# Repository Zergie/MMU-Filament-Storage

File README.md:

<p align="center">

</p>

YAMMU is an open, Voron-inspired multi-material unit for FFF printers. It combines eight filament paths, enclosed heated storage, BLDC-driven loading, filament sensing, custom electronics, and Klipper-based control in one machine.

> [!IMPORTANT]
> **YAMMU is a work in progress.** The current goal is reliable loading and unloading before or at the start of a print. Multi-color and multi-material printing are planned, but are not the present focus.

## See the machine

| Complete enclosure | Twin spool carrier | Heated chamber | Custom electronics bay |
| :---: | :---: | :---: | :---: |
|  |  |  |  |

## One system, four jobs

- **Store** — eight spools live in two enclosed drawers built around 2020 extrusion.
- **Dry** — the sealed filament chamber is heated for dry storage while printing.
- **Move** — two BLDC-driven feeders load filament through short inlet paths and toward the extruder.
- **Verify** — switches at the splitter and toolhead let the control system confirm filament progress.

## Built as open hardware

The repository contains the mechanical, electrical, firmware, and assembly material needed to follow the project—not just product renders.

| Area | What is included | Start here |
| --- | --- | --- |
| Mechanical | STEP assembly, printable STLs, and panel DXFs | [CAD](./CAD) · [STLs](./STLs) · [DXFs](./Drawings_DXFs) |
| Electronics | Main, connector, and sensor-board source and manufacturing files | [PCB files](./PCB) - new version soon! |
| Firmware | RP2040 build notes and YAMMU configuration for Klipper / Happy Hare | [Firmware guide](./Firmware/README.md) - new version soon! |
| Assembly | Illustrated assembly manual | [Open the PDF](./Manual/Assembly.pdf) |

## Start exploring

1. Inspect the [STEP assembly](./CAD/Assembly.step) or browse the ready-to-print [STLs](./STLs).
2. Read the [assembly manual](./Manual/Assembly.pdf) to understand the current mechanical build.
3. (unfinished) Review the [PCB feature set](./PCB/README.md) and manufacturing files.
4. (unfinished) Follow the [firmware guide](./Firmware/README.md) for the current RP2040, Klipper, and Happy Hare setup.

## Current roadmap

[View v1.0 progress](https://github.com/Zergie/YAMMU/issues?q=is%3Aissue%20milestone%3Av1.0)
[View v1.1 progress](https://github.com/Zergie/YAMMU/issues?q=is%3Aissue%20milestone%3Av1.1)

## Help build YAMMU

The project especially needs help with prototype testing, CAD, electronics, firmware, and documentation. If you can test the current iteration or improve one part of the system, open an issue or pull request—or join the [YAMMU Discord](https://discord.gg/QSjW5CMHZC).

## Credits and related projects

YAMMU builds on ideas and parts from the wider open-source 3D-printing community, including [Voron Trident](https://github.com/VoronDesign/Voron-Trident), [ERCF v2](https://github.com/Enraged-Rabbit-Community/ERCF_v2), and several community designs documented in the repository history. Review source licenses before redistributing derived parts.

<details>
<summary><strong>Third-party parts and original licenses</strong></summary>

- [Voron Trident](https://github.com/VoronDesign/Voron-Trident) parts — GNU GPL v3
- [ERCF v2](https://github.com/Enraged-Rabbit-Community/ERCF_v2) parts — GNU GPL v3
- [Stronger Compact Spool Auto-Rewinder](https://www.printables.com/model/784434-stronger-compact-spool-auto-rewinder) by rans_1668459 — GNU GPL v2
- [Voron 2.4 front panel handle, hinge, and magnet latch](https://www.printables.com/model/371692-voron-24-front-panel-handle-hinge-magnet-latch/files) by Jason_116929 — CC BY-SA
- [Removable panel/door kit for Voron V2/Trident](https://www.printables.com/model/702768-kit-for-removable-panelsdoors-for-voron-v2trident-/files) by Victor Mateus Oliveira — GNU GPL v3
- [WAGO 221-415 extrusion mount](https://www.printables.com/model/869020-wago-221-415-extrusion-mount-1by5-and-2by5) by Artxime — GNU GPL v3
- [LRS-200 DIN rail mount](https://www.printables.com/model/254538-lrs-200-din-rail-mount) by CrazyIvan359 — Creative Commons 4.0

</details>

Other MMU projects worth exploring include [ERCF v2](https://github.com/Enraged-Rabbit-Community/ERCF_v2), [8-Track](https://github.com/ArmoredTurtle/8-Track-Raven-Alpha), [Primitive Infinite Spool System](https://github.com/Esoterical/PrinterMods/tree/main/Primitive%20Infinite%20Spool%20System), [TradRack](https://github.com/Annex-Engineering/TradRack), and Prusa MMU3.

## License

Repository content is provided under the [GNU General Public License v3.0](./LICENSE). Third-party parts retain their original licenses.

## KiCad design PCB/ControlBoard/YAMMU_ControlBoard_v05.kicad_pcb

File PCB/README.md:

<p align="center">

</p>

This directory contains the editable KiCad design and manufacturing data for the **YAMMU Control Board v05**. The 100 × 60 mm board brings the RP2040 controller, motor and heater control, fan outputs, servos, end stops, analog sensors, I²C, and power regulation onto one board.

## Board preview

| Component side | Solder side |
| :---: | :---: |
|  |  |

| Design fact | Checked-in value |
| --- | --- |
| Board revision | `05` |
| KiCad format | KiCad `9.0` |
| Outline | approximately `100 × 60 mm` |
| Board thickness | `1.6 mm` |
| Copper stack | `4 layers` |
| Assembly side | Top-side placement data; the bottom placement file contains no components |
| Placement records | 220 top-side entries |
| DRC snapshot | [0 violations, 0 unconnected pads](./ControlBoard/DRC.rpt) on 2026-07-11 |

## Find the right file

| Use | File |
| --- | --- |
| Open the complete design | [`YAMMU_ControlBoard_v05.kicad_pro`](./ControlBoard/YAMMU_ControlBoard_v05.kicad_pro) |
| Edit the PCB | [`YAMMU_ControlBoard_v05.kicad_pcb`](./ControlBoard/YAMMU_ControlBoard_v05.kicad_pcb) |
| Read the schematic | [Schematic PDF](./ControlBoard/OutputJob/Schematics/YAMMU_ControlBoard_v05.pdf) |
| Manufacture bare boards | [Gerber + drill ZIP](./ControlBoard/OutputJob/YAMMU_ControlBoard_v05_Gerber.zip) |
| Order SMT assembly | [BOM](./ControlBoard/OutputJob/BOM/YAMMU_ControlBoard_v05_BOM.xlsx) + [top-side CPL](./ControlBoard/OutputJob/Centroid/TopCentroid.xlsx) |
| Hand-assemble or inspect | [Interactive BOM](./ControlBoard/Interactive%20Bom/ibom.html) |
| Check component outlines | [Front fabrication drawing](./ControlBoard/OutputJob/BestPlan/YAMMU_ControlBoard_v05-F_Fab.pdf) · [Back fabrication drawing](./ControlBoard/OutputJob/BestPlan/YAMMU_ControlBoard_v05-B_Fab.pdf) |

## Order a bare PCB

[JLCPCB](https://jlcpcb.com/) is one example board house; the same release files can be used with another manufacturer. Prices, capabilities, and form labels change, so treat the provider's current documentation as authoritative.

1. Open the board house's PCB quote page and upload the **ZIP itself**. For JLCPCB, use the [Gerber + drill ZIP](./ControlBoard/OutputJob/YAMMU_ControlBoard_v05_Gerber.zip).
2. Compare the detected result with the design: approximately **100 × 60 mm**, **4 copper layers**, and **1.6 mm** finished thickness. Select the required material, copper weight, solder-mask color, surface finish, quantity, and any other fabrication options; do not rely on automatic detection for choices that are not encoded in the Gerbers.
3. Open the provider's Gerber viewer. Inspect all four copper layers, the continuous board outline, all drills and slots, both masks, and both silkscreens.
4. Save the item to the cart, review manufacturing warnings, shipping, tax, and lead time, then submit the order.

JLCPCB's current walkthrough is available in its [official PCB ordering guide](https://jlcpcb.com/help/article/how-do-i-place-an-order). The online preview is a useful final check, but it does not replace reviewing the KiCad design and release contents.

## Order SMT assembly

An assembly order needs three data sets:

| Upload | What it tells the assembler | This repository |
| --- | --- | --- |
| **Gerbers + drills** | How to fabricate the bare board | [`YAMMU_ControlBoard_v05_Gerber.zip`](./ControlBoard/OutputJob/YAMMU_ControlBoard_v05_Gerber.zip) |
| **BOM** | Which part belongs at each reference designator | [`YAMMU_ControlBoard_v05_BOM.xlsx`](./ControlBoard/OutputJob/BOM/YAMMU_ControlBoard_v05_BOM.xlsx) |
| **CPL / centroid / pick-and-place** | Each component's X/Y position, rotation, and board side | [`TopCentroid.xlsx`](./ControlBoard/OutputJob/Centroid/TopCentroid.xlsx) |

The BOM contains `Designator`, `Comment`, `Footprint`, `Amount`, and `JLCPCB Part #` columns. The CPL contains `Designator`, `Mid X`, `Mid Y`, `Rotation`, and `Layer`. The reference designators must match between the two files.

For a JLCPCB PCBA order:

1. Start a PCB order, upload the corrected Gerber ZIP, and enable **PCB Assembly** before checkout.
2. Select top-side assembly. The current top CPL has 220 placement records. The bottom CPL has no components and is not used for assembly.
3. Upload the BOM and top-side CPL, then let the service process and match them.
4. Review every unmatched or substituted component. Confirm value, package, manufacturer part number or JLCPCB/LCSC part number, stock, and quantity. “No part selected” means that item will not be fitted.
5. Inspect the placement preview at high zoom. Check connector orientation, polarized capacitors and diodes, IC pin 1, rotations, and the board origin. Do not approve the job solely because the files were accepted.
6. Confirm which through-hole, module, connector, or otherwise unsupported parts must be installed by hand after delivery.

JLCPCB documents the current flow in its [official PCBA ordering guide](https://jlcpcb.com/help/article/how-do-i-place-a-pcba-order). Its [BOM/CPL preparation guidance](https://jlcpcb.com/help/article/advice-for-bom-and-cpl-files-preparation) explains reference matching, supported headers, coordinates, and common upload problems.

> [!IMPORTANT]
> Component availability and assembly capabilities are live manufacturing constraints, not properties of this repository. Always re-check part matches and the placement preview for the specific order.

## Use the Interactive BOM

[`Interactive Bom/ibom.html`](./ControlBoard/Interactive%20Bom/ibom.html) is a self-contained browser view generated from the PCB. Download or clone the repository and open the file locally—no KiCad installation or web server is required.

Use it to:

- click a BOM row and highlight the matching footprints on the board;
- pan, zoom, and switch between board sides;
- search by reference, value, or footprint;
- group identical parts and inspect their board locations;
- tick off parts while hand-placing or checking a finished assembly.

The Interactive BOM is an **assembly and inspection aid**. It is not the BOM spreadsheet, not pick-and-place data, and not a file to upload for SMT assembly. Use the `.xlsx` BOM and CPL listed above for the manufacturer.

## License

This PCB is part of the YAMMU open-hardware project. See the repository's [GNU GPL v3.0 license](../LICENSE).

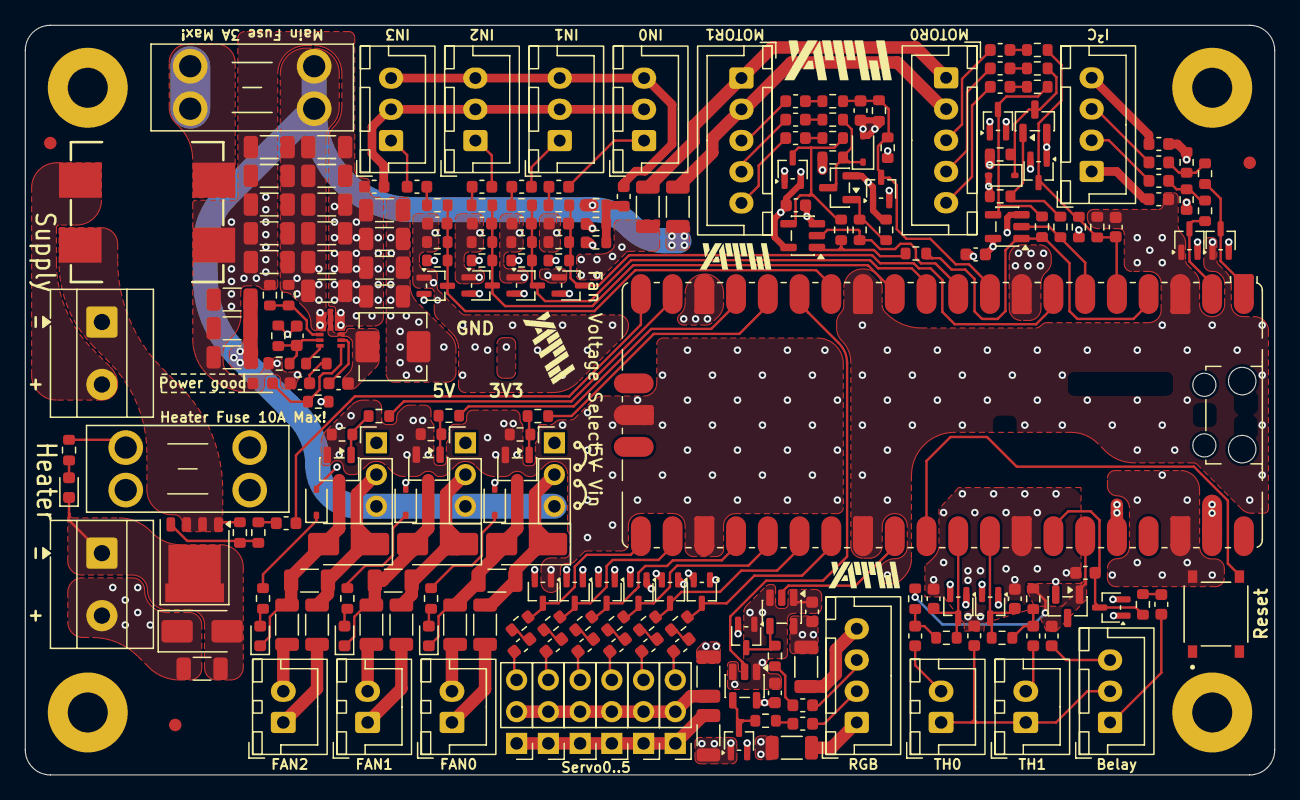
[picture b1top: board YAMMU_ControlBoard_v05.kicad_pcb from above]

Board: 8 copper layers, 100.0 x 60.0 mm, 234 parts (0 on the bottom side), 137 nets.

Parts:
C1, C3: 1nF; C_0603_1608Metric
C1.1, C1.2, C1.3, C1.4, C1.5, C1.6, C1.7, C7, C8, C9, C10, C11, C12, C13: 10µF 50V; C_1206_3216Metric
C2, C4, C5, C14: 10nF; C_0603_1608Metric
C2.1, C2.2, C2.3, C2.4: 100µF/6,3V; C_1206_3216Metric
C3.1, C16, C17, C20, C21, C22, C23, C24: 100nF; C_0603_1608Metric
C4.1: 47pF; C_0603_1608Metric
C5.1: 3,3nF; C_0603_1608Metric
C6, C15, C18, C19: 2,2µF; C_1206_3216Metric
D1, D2, D3, D4, D6, D7, D8, D9, D11, D15, D17, D21, D22, D23, D24, D25, D31, D32, D33, D34, D35: BAT54SW; SOT-323_SC-70
D5, D10: BZT52C4V7S; D_SOD-323
D12, D16, D18, D27, D28: RED; LED_0603_1608Metric
D13, D19, D29: 1N4148; D_SOD-323
D14, D20, D26, D30: SS34; D_SMA
F1: 3A; Fuseholder_Blade_Mini_Keystone_3568
F2: 10A; Fuseholder_Blade_Mini_Keystone_3568
FB1, FB2, FB3, FB4, FB5, FB6, FB7, FB8, FB9, FB10, FB11, FB13, FB15, FB16, FB18, FB20, FB21, FB22, FB23, FB24, FB25, FB26, FB34, FB36, FB38, FB39, FB40, FB41, FB42, FB43: 600Ohm 200mA; L_0603_1608Metric
FB12, FB14, FB17, FB19, FB28, FB29, FB30, FB31, FB32, FB33, FB35, FB37: 600Ohm 3A; L_1206_3216Metric
FID1, FID2, FID3: Fiducial; Fiducial_1mm_Mask2mm
H1, H2, H3, H4: M3; MountingHole_3.2mm_M3_Pad
IC1: AP63356DV-7; AP63356DV7
IC2: RaspberryPi_Pico; RaspberryPi_Pico_SMD_HandSolder
J1, J4, J7, J11, J23: Conn_01x03; JST_XH_B3B-XH-A_1x03_P2.50mm_Vertical
J2, J5: Conn_01x05; JST_XH_B5B-XH-A_1x05_P2.50mm_Vertical
J3, J6, J10, J13, J15, J17: Conn_01x03_Pin; PinHeader_1x03_P2.54mm_Vertical_HighDensity
J8, J12, J14, J16, J20: Conn_01x02; JST_XH_B2B-XH-A_1x02_P2.50mm_Vertical
J9, J19: Screw_Terminal_01x02; JL301-50002U02
J21, J22: Conn_01x04; JST_XH_B4B-XH-A_1x04_P2.50mm_Vertical
JP2, JP3, JP4: Jumper_3_Open; PinHeader_1x03_P2.54mm_Vertical_HighDensity
L1: 6,8µH; L_APV_APH0530
L2: 1kΩ@100MHz 2 6A 80V; ACM1211
Q1, Q2: 2N7002; SOT-23
Q3, Q4, Q6: AO3400A; SOT-23-3
Q5: HY1904C2; PQFN-8-EP_6x5mm_P1.27mm_Generic
R1, R14, R35, R36, R37, R64: 0R; R_0603_1608Metric
R1.1: 105K; R_0603_1608Metric
R2, R3, R6, R7, R10, R15, R16, R19, R20, R23, R28, R30, R39, R41: 150K; R_0603_1608Metric
R2.1, R51: 20K; R_0603_1608Metric
R3.1, R13, R26, R34, R44, R45, R48, R53, R56: 47K; R_0603_1608Metric
R4, R4.1, R5, R17, R18, R29, R40: 10K; R_0603_1608Metric
R5.1: 38K3; R_0603_1608Metric
R8, R9, R11, R21, R22, R24, R32, R42, R47, R50, R57, R58: 220R; R_0603_1608Metric
R12, R25, R33, R43, R52, R55, R60, R62: 100R; R_0603_1608Metric
R27, R31, R38, R54: 1K; R_0603_1608Metric
R46, R49, R59, R61, R63: 4K7; R_0603_1608Metric
SW1: SW_MEC_5E; SW_TS-1187A-B-A-B
U1, U2: SN74AHCT1G86DBVR; SOT-23-5
U3: LM4040A30IDBZR; SOT-23
U4, U5: SN74AHCT1G125DBVR; SOT-23-5

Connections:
+3V3: C23.1, C24.1, D1.2 (K), D2.2 (K), D3.2 (K), D4.2 (K), D6.2 (K), D7.2 (K), D8.2 (K), D9.2 (K), D11.2 (K), D13.2 (A), D15.2 (K), D17.2 (K), D19.2 (A), D21.2 (K), D22.2 (K), D23.2 (K), D24.2 (K), D25.2 (K), D29.2 (A), D33.2 (K), D34.2 (K), D35.2 (K), FB39.2, IC2.36 (3V3), R2.1, R3.1, R15.1, R16.1, R28.1, R31.1, R35.1, R39.1, R59.2, R61.2, U1.5 (VCC), U2.5 (VCC)
+5V: C2.1.1, C2.2.1, C2.3.1, C2.4.1, C4.1.2, C20.1, C21.1, D31.2 (K), D32.2 (K), FB30.2, FB35.1, IC2.39 (VSYS), JP2.1 (A), JP3.1 (A), JP4.1 (A), L1.2, R1.1.1, R36.1, U4.5 (VCC), U5.5 (VCC)
/AnalogSensors/AnalogSignals.Belay: C22.1, D35.3 (COM), IC2.34 (GPIO28_ADC2), R63.2
/AnalogSensors/AnalogSignals.TH0: C16.1, D22.3 (COM), IC2.31 (GPIO26_ADC0), R46.2
/AnalogSensors/AnalogSignals.TH1: C17.1, D24.3 (COM), IC2.32 (GPIO27_ADC1), R49.2
/AnalogSensors/Belay/GNDsensor: FB23.2, J14.1, J16.1, J23.2
/AnalogSensors/Vref: FB42.2, IC2.35 (ADC_VREF), R45.1, R48.1, U3.1 (K)
/EndStops/EndStop0: C2.1, D2.3 (COM), IC2.7 (GPIO5), R3.2, R5.2, R7.1
/EndStops/EndStop1: C4.1, D7.3 (COM), IC2.11 (GPIO8), R16.2, R18.2, R20.1
/EndStops/EndStop2: C5.1, D11.3 (COM), IC2.12 (GPIO9), R28.2, R29.2, R30.1
/EndStops/EndStop3: C14.1, D17.3 (COM), IC2.14 (GPIO10), R39.2, R40.2, R41.1
/EndStops/Input0/GNDin: FB20.2, J1.2, J4.2, J7.2, J11.2
/EndStops/Input0/Input_In: FB1.1, J1.1
/EndStops/Input0/Vin: FB15.1, J1.3, J4.3, J7.3, J11.3
/EndStops/Input1/Input_In: FB6.1, J4.1
/EndStops/Input2/Input_In: FB11.1, J7.1
/EndStops/Input3/Input_In: FB16.1, J11.1
/FansOut/FanEnable0: IC2.16 (GPIO12), R33.1
/FansOut/FanEnable1: IC2.17 (GPIO13), R43.1
/FansOut/FanEnable2: IC2.19 (GPIO14), R55.1
/FansOut/FanOut0/1N4148_A: D13.1 (K), R27.1
/FansOut/FanOut0/Fout+: FB12.2, J8.1
/FansOut/FanOut0/Fout-: FB14.1, J8.2
/FansOut/FanOut0/Gate: Q3.1 (G), R33.2, R34.1
/FansOut/FanOut0/LED_A: D12.2 (A), R27.2
/FansOut/FanOut1/1N4148_A: D19.1 (K), R38.1
/FansOut/FanOut1/Fout+: FB17.2, J12.1
/FansOut/FanOut1/Fout-: FB19.1, J12.2
/FansOut/FanOut1/Gate: Q4.1 (G), R43.2, R44.1
/FansOut/FanOut1/LED_A: D18.2 (A), R38.2
/FansOut/FanOut2/1N4148_A: D29.1 (K), R54.1
/FansOut/FanOut2/Fout+: FB31.2, J20.1
/FansOut/FanOut2/Fout-: FB32.1, J20.2
/FansOut/FanOut2/Gate: Q6.1 (G), R55.2, R56.1
/FansOut/FanOut2/LED_A: D28.2 (A), R54.2
/HeaterOut/EN_IN: FB26.1, R52.1
/HeaterOut/Enable: FB26.2, IC2.20 (GPIO15)
/HeaterOut/Gate: Q5.4 (G), R52.2, R53.1
/HeaterOut/Hout+: C18.1, D26.1 (K), F2.2, J19.2, R51.1
/HeaterOut/Hout-: C18.2, D26.2 (A), D27.1 (K), J19.1, Q5.5 (D)
/HeaterOut/LED_A: D27.2 (A), R51.2
/HeaterOut/Vin+: F2.1, J9.2, L2.1
/I²C_Out/SCL_Out: FB40.2, J22.2
/I²C_Out/SDA_Out: FB38.2, J22.3
/MCU/BLDC0.DIR: IC2.4 (GPIO2), R14.1, R64.1, U2.1
/MCU/BLDC0.PWM: IC2.6 (GPIO4), R25.1, U2.2
/MCU/BLDC0.TACHO: C3.1, D6.3 (COM), IC2.5 (GPIO3), R15.2, R17.1, R19.1
/MCU/BLDC1.PWM: IC2.10 (GPIO7), R12.1, U1.2
/MCU/BLDC1.TACHO: C1.1, D1.3 (COM), IC2.9 (GPIO6), R2.2, R4.1, R6.1
/MCU/I2C.SCL: D34.3 (COM), IC2.2 (GPIO1), R62.1
/MCU/I2C.SDA: D33.3 (COM), IC2.1 (GPIO0), R60.1
/MCU/RGB.CLK: IC2.15 (GPIO11), U5.2
/MCU/RGB.DATA: IC2.29 (GPIO22), U4.2
/Motors/BLDC0/DIR_Mot: FB8.1, J5.5
/Motors/BLDC0/GND_Mot: FB29.1, J2.1, J5.1
/Motors/BLDC0/PWM_Mot: FB10.1, J5.4
/Motors/BLDC0/Tacho_Mot: FB7.2, J5.3
/Motors/BLDC0/V_Mot: FB28.2, J2.2, J5.2
/Motors/BLDC1.DIR: R1.1, R64.2, U1.1
/Motors/BLDC1/DIR_Mot: FB3.1, J2.5
/Motors/BLDC1/PWM_Mot: FB5.1, J2.4
/Motors/BLDC1/Tacho_Mot: FB2.2, J2.3
/Power/Vreg/BST: C3.1.1, IC1.6 (BST)
/Power/Vreg/COMP: IC1.4 (COMP), R5.1.1
/Power/Vreg/EN: IC1.2 (EN), R3.1.2, R4.1.1
/Power/Vreg/FB: C4.1.1, IC1.3 (FB), R1.1.2, R2.1.1
/Power/Vreg/PG: D16.2 (A), IC1.5 (PG), R31.2
/Power/Vreg/SW: C3.1.2, IC1.7 (SW), IC1.9 (SW), L1.1
/RGB_LED_Out/Clock_out: FB36.2, J21.2
/RGB_LED_Out/Data_out: FB34.2, J21.3
/ServosOut/Servo0/GNDservo: FB33.2, J3.1, J6.1, J10.1, J13.1, J15.1, J17.1
/ServosOut/Servo0/Signal_out: FB18.2, J13.3
/ServosOut/Servo0/Vservo: FB30.1, J3.2, J6.2, J10.2, J13.2, J15.2, J17.2
/ServosOut/Servo1/Signal_out: FB4.2, J3.3
/ServosOut/Servo2/Signal_out: FB9.2, J6.3
/ServosOut/Servo3/Signal_out: FB13.2, J10.3
/ServosOut/Servo4/Signal_out: FB22.2, J15.3
/ServosOut/Servo5/Signal_out: FB25.2, J17.3
/ServosOut/ServoSignal0: D21.3 (COM), IC2.21 (GPIO16), R42.1
/ServosOut/ServoSignal1: D4.3 (COM), IC2.22 (GPIO17), R9.1
/ServosOut/ServoSignal2: D9.3 (COM), IC2.24 (GPIO18), R22.1
/ServosOut/ServoSignal3: D15.3 (COM), IC2.25 (GPIO19), R32.1
/ServosOut/ServoSignal4: D23.3 (COM), IC2.26 (GPIO20), R47.1
/ServosOut/ServoSignal5: D25.3 (COM), IC2.27 (GPIO21), R50.1
/Vin-: H1.1, H2.1, J9.1, L2.3, Q5.1 (S), Q5.2 (S), Q5.3 (S), R53.2
AGND: C16.2, C17.2, C22.2, FB23.1, IC2.33 (AGND), U3.2 (A)
GND: C1.2, C1.1.2, C1.2.2, C1.3.2, C1.4.2, C1.5.2, C1.6.2, C1.7.2, C2.2, C2.1.2, C2.2.2, C2.3.2, C2.4.2, C3.2, C4.2, C5.2, C5.1.1, C7.2, C8.2, C9.2, C10.2, C11.2, C12.2, C13.2, C14.2, C20.2, C21.2, C23.2, C24.2, D1.1 (A), D2.1 (A), D3.1 (A), D4.1 (A), D5.2 (A), D6.1 (A), D7.1 (A), D8.1 (A), D9.1 (A), D10.2 (A), D11.1 (A), D15.1 (A), D16.1 (K), D17.1 (A), D21.1 (A), D22.1 (A), D23.1 (A), D24.1 (A), D25.1 (A), D31.1 (A), D32.1 (A), D33.1 (A), D34.1 (A), D35.1 (A), FB20.1, FB29.2, FB33.1, FB37.1, FB41.1, IC1.8 (GND), IC2.3 (GND), IC2.8 (GND), IC2.13 (GND), IC2.18 (GND), IC2.23 (GND), IC2.28 (GND), IC2.38 (GND), IC2.D2 (GND), L2.4, Q1.2 (S), Q2.2 (S), Q3.2 (S), Q4.2 (S), Q6.2 (S), R2.1.2, R4.1.2, R6.2, R7.2, R13.1, R19.2, R20.2, R26.1, R30.2, R34.2, R41.2, R44.2, R56.2, SW1.B, U1.3 (GND), U2.3 (GND), U4.1, U4.3 (GND), U5.1, U5.3 (GND)
unnamed: C5.1.2, R5.1.2
unnamed: D3.3 (COM), R1.2, R8.1, U1.4
unnamed: D5.1 (K), Q1.3 (D), R10.1, R11.1
unnamed: D8.3 (COM), R14.2, R21.1, U2.4
unnamed: D10.1 (K), Q2.3 (D), R23.1, R24.1
unnamed: C6.2, D12.1 (K), D14.2 (A), FB14.2, Q3.3 (D)
unnamed: C6.1, D14.1 (K), FB12.1, JP2.2 (C)
unnamed: C15.2, D18.1 (K), D20.2 (A), FB19.2, Q4.3 (D)
unnamed: C15.1, D20.1 (K), FB17.1, JP3.2 (C)
unnamed: C19.2, D28.1 (K), D30.2 (A), FB32.2, Q6.3 (D)
unnamed: C19.1, D30.1 (K), FB31.1, JP4.2 (C)
unnamed: D31.3 (COM), R57.1, U4.4
unnamed: D32.3 (COM), R58.1, U5.4
unnamed: F1.1, L2.2
unnamed: FB1.2, R5.1
unnamed: FB2.1, R4.2
unnamed: FB3.2, R8.2
unnamed: FB4.1, R9.2
unnamed: FB5.2, R11.2
unnamed: FB6.2, R18.1
unnamed: FB7.1, R17.2
unnamed: FB8.2, R21.2
unnamed: FB9.1, R22.2
unnamed: FB10.2, R24.2
unnamed: FB11.2, R29.1
unnamed: FB13.1, R32.2
unnamed: FB15.2, R35.2, R36.2, R37.2
unnamed: FB16.2, R40.1
unnamed: FB18.1, R42.2
unnamed: FB21.2, R45.2, R46.1
unnamed: FB22.1, R47.2
unnamed: FB24.2, R48.2, R49.1
unnamed: FB25.1, R50.2
unnamed: FB34.1, R57.2
unnamed: FB36.1, R58.2
unnamed: FB38.1, R59.1, R60.2
unnamed: FB40.1, R61.1, R62.2
unnamed: FB43.2, R63.1
unnamed: IC2.30 (RUN), SW1.D
unnamed: FB21.1, J14.2
unnamed: FB24.1, J16.2
unnamed: FB37.2, J21.1
unnamed: FB35.2, J21.4
unnamed: FB41.2, J22.1
unnamed: FB39.1, J22.4
unnamed: FB43.1, J23.1
unnamed: FB42.1, J23.3
unnamed: Q1.1 (G), R12.2, R13.2
unnamed: Q2.1 (G), R25.2, R26.2
VSS: C1.1.1, C1.2.1, C1.3.1, C1.4.1, C1.5.1, C1.6.1, C1.7.1, C7.1, C8.1, C9.1, C10.1, C11.1, C12.1, C13.1, F1.2, FB28.1, IC1.1 (VIN), JP2.3 (B), JP3.3 (B), JP4.3 (B), R3.1.1, R10.2, R23.2, R37.1
